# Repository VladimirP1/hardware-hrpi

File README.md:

# A simple add-on board for Raspberry Pi to run a downstream verion of APM (https://github.com/VladimirP1/ardupilot) (waf configure --board=hrpi)

This board has been designed considering this technology: http://cxem.net/master/45.php

The APM port requires servod form ServoBlaster (https://github.com/richardghirst/PiBits/tree/master/ServoBlaster/user) to be in PATH.

Only one hardware UART is available on the Pi, so either GPS or telemetry should be connected over USB.

# RT-preempt
- I have built my RT kernel from official Rasberry Pi Foundation's kernel patched with corresponding RT version.
- If your pi does not boot with RT-patched kernel try adding sdhci_bcm2708.enable_llm=0 to cmdline. If you expirince hangs with RT kernel try to add dwc_otg.fiq_enable=0 to cmdline.

# WARNING
-This board uses 10k resistors to protect Raspberry pi's inputs from 5v and relies on its internal protection diodes.
Earlier revision of the board with external diodes work OK, but the current revision is UNTESTED.

-ALWAYS FLASH FIRMWARE BEFORE PLUGGING IN ARDUINO NANO OR YOU RISK TO BURN YOUR PI (It can happen if either of A4 and A5 is driven HIGH) !!!

-Only tested on RPI 2

# Repo structure
- doc: documentation
- src/kicad/hrpi: KICAD sources
- src/arduino/i2c-adc-rc: Arduino sources

# Important notes
- MPU6000 uses MOSI, MISO, SCLK, NSS2, GND, 3V3 form the SPI connector.

# Details
- RC input is recieved by arduino nano, then it is read out by RPI over i2c.
- RC output is done over RPI's gpio using ServoBlaster (https://github.com/richardghirst/PiBits/tree/master/ServoBlaster/user).
- Sensors must be connected externally by SPI and I2C. Madarnatory sensors: MPU6000(SPI), HMC5883L(I2C), MS5611(I2C, except rover).
Examples of breakout boards: GY-63, GY-273 and Mikroe MPU imu click.
- Power must be provided either over the RC rail with P9 closed or the P3 connector

# Serial pinout

# Connecting 3DR radio

If you have two ground modules you can plug one into your PC, one into RPI. They will communicate.
If they do not, make sure that the have same net id.
You can also connect to RPI without 3DR radio, over wifi.

# I2C pinout

# SPI pinout

# How to connect ACC/GYRO

# ADC pinout

# RC main pinout

# RC aux pinout
AUX0-AUX4=RC8-RC13

# Todo
- handle RC OK led by software
- maybe upstream APM
- fix default accel orientation

# Render

# License
The repo contents are licensed under the MIT license

Copyright (c) 2016 Vladimir Pinchuk

Permission is hereby granted, free of charge, to any person obtaining a copy of this software and associated documentation files (the "Software"), to deal 
in the Software without restriction, including without limitation the rights to use, copy, modify, merge, publish, distribute, sublicense, and/or sell copies of 
the Software, and to permit persons to whom the Software is furnished to do so, subject to the following conditions:

The above copyright notice and this permission notice shall be included in all copies or substantial portions of the Software.

THE SOFTWARE IS PROVIDED "AS IS", WITHOUT WARRANTY OF ANY KIND, EXPRESS OR IMPLIED, INCLUDING BUT NOT LIMITED TO THE WARRANTIES OF MERCHANTABILITY, FITNESS 
FOR A PARTICULAR PURPOSE AND NONINFRINGEMENT. IN NO EVENT SHALL THE AUTHORS OR COPYRIGHT HOLDERS BE LIABLE FOR ANY CLAIM, DAMAGES OR OTHER LIABILITY, WHETHER IN 
AN ACTION OF CONTRACT, TORT OR OTHERWISE, ARISING FROM, OUT OF OR IN CONNECTION WITH THE SOFTWARE OR THE USE OR OTHER DEALINGS IN THE SOFTWARE.

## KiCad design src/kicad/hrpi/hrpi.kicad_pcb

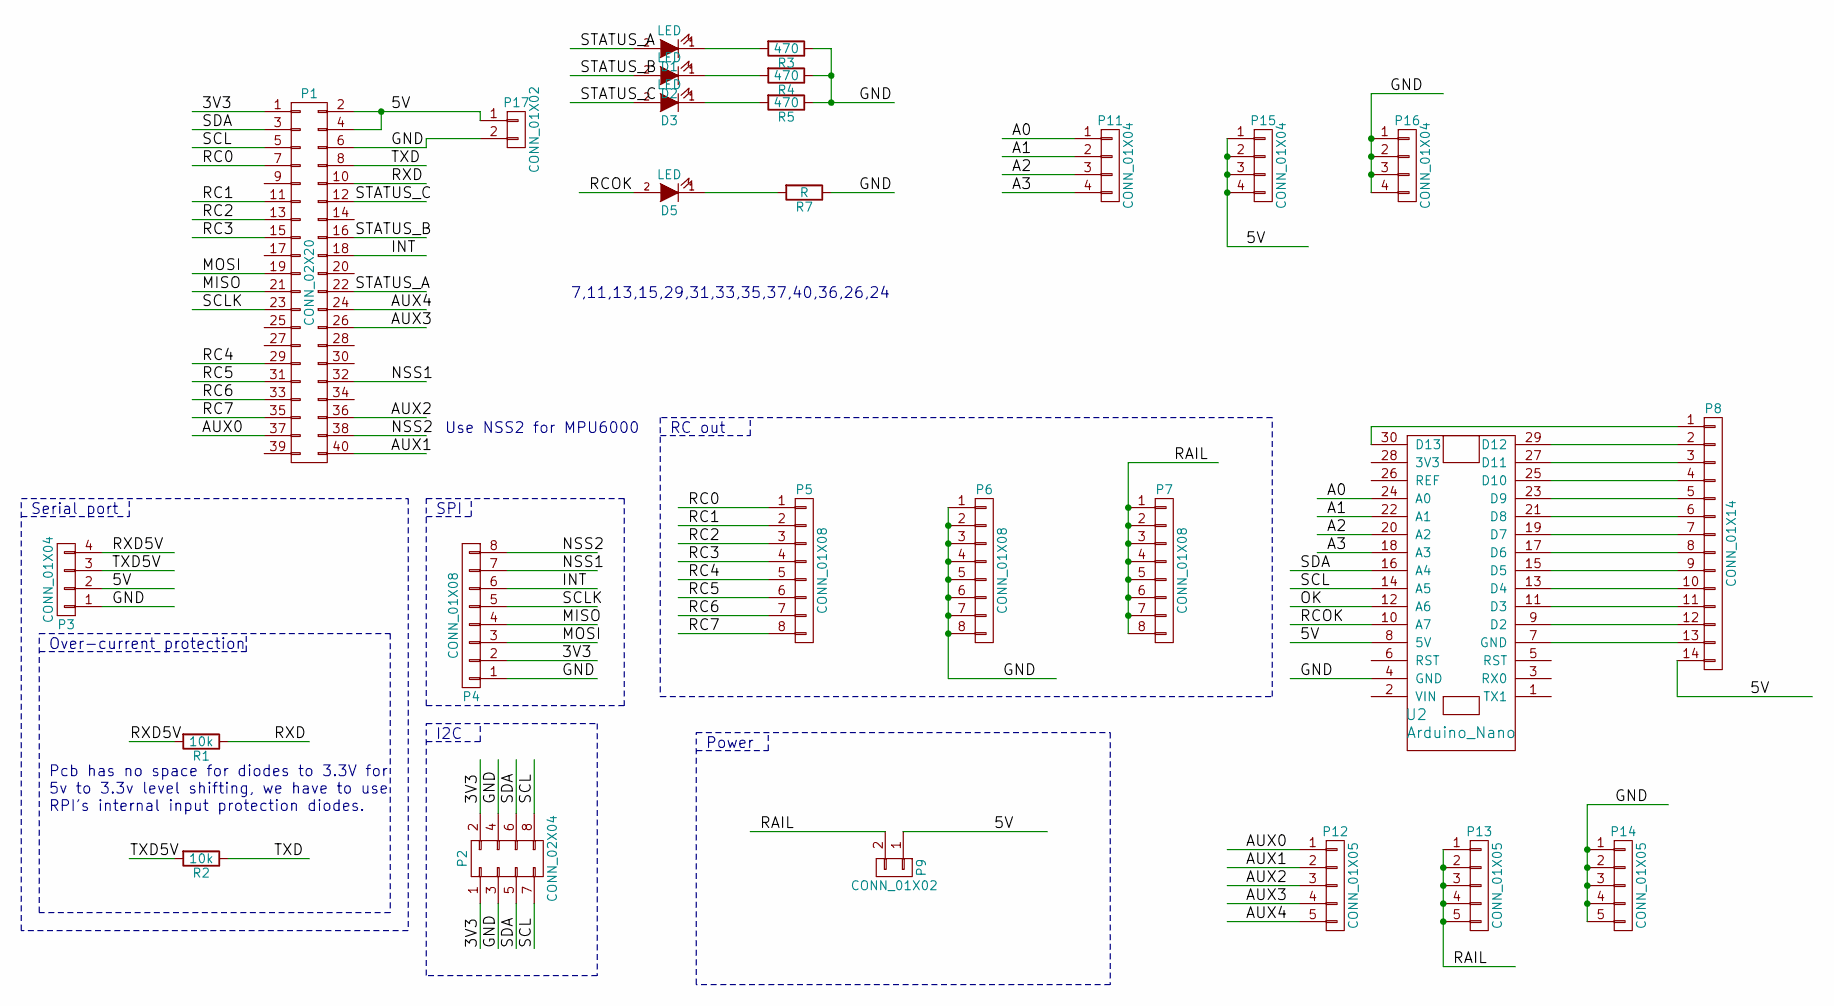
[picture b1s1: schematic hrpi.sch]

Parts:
D1, D2, D3, D5: LED; LED-3MM
P1: CONN_02X20; Pin_Header_Straight_2x20
P2: CONN_02X04; Pin_Header_Straight_2x04
P3, P11, P15, P16: CONN_01X04; Pin_Header_Straight_1x04
P4, P5, P6, P7: CONN_01X08; Pin_Header_Straight_1x08
P8: CONN_01X14; Pin_Header_Straight_1x14
P9, P17: CONN_01X02; Pin_Header_Straight_1x02
P12, P13, P14: CONN_01X05; Pin_Header_Straight_1x05
R1, R2: 10k; R_0805_HandSoldering
R3, R4, R5: 470; R_0805_HandSoldering
R7: R; R_0805_HandSoldering
U2: Arduino_Nano; arduino_nano

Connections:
/3V3: P1.1, P2.1, P2.2, P4.2
/5V: P1.2, P1.4, P3.2, P8.14, P9.1, P15.1, P15.2, P15.3, P15.4, P17.1, U2.8 (5V)
/A0: P11.1, U2.24 (A0)
/A1: P11.2, U2.22 (A1)
/A2: P11.3, U2.20 (A2)
/A3: P11.4, U2.18 (A3)
/AUX0: P1.37, P12.1
/AUX1: P1.40, P12.2
/AUX2: P1.36, P12.3
/AUX3: P1.26, P12.4
/AUX4: P1.24, P12.5
/GND: P1.6, P2.3, P2.4, P3.1, P4.1, P6.1, P6.2, P6.3, P6.4, P6.5, P6.6, P6.7, P6.8, P14.1, P14.2, P14.3, P14.4, P14.5, P16.1, P16.2, P16.3, P16.4, P17.2, R3.1, R4.1, R5.1, R7.1, U2.4 (GND)
/INT: P1.18, P4.6
/MISO: P1.21, P4.4
/MOSI: P1.19, P4.3
/NSS1: P1.32, P4.7
/NSS2: P1.38, P4.8
/RAIL: P7.1, P7.2, P7.3, P7.4, P7.5, P7.6, P7.7, P7.8, P9.2, P13.1, P13.2, P13.3, P13.4, P13.5
/RC0: P1.7, P5.1
/RC1: P1.11, P5.2
/RC2: P1.13, P5.3
/RC3: P1.15, P5.4
/RC4: P1.29, P5.5
/RC5: P1.31, P5.6
/RC6: P1.33, P5.7
/RC7: P1.35, P5.8
/RCOK: D5.2 (A), U2.10 (A7)
/RXD: P1.10, R1.1
/RXD5V: P3.4, R1.2
/SCL: P1.5, P2.7, P2.8, U2.14 (A5)
/SCLK: P1.23, P4.5
/SDA: P1.3, P2.5, P2.6, U2.16 (A4)
/STATUS_A: D1.2 (A), P1.22
/STATUS_B: D2.2 (A), P1.16
/STATUS_C: D3.2 (A), P1.12
/TXD: P1.8, R2.1
/TXD5V: P3.3, R2.2
unnamed: D1.1 (K), R3.2
unnamed: D2.1 (K), R4.2
unnamed: D3.1 (K), R5.2
unnamed: D5.1 (K), R7.2
unnamed: P8.1, U2.30 (D13)
unnamed: P8.2, U2.29 (D12)
unnamed: P8.3, U2.27 (D11)
unnamed: P8.4, U2.25 (D10)
unnamed: P8.5, U2.23 (D9)
unnamed: P8.6, U2.21 (D8)
unnamed: P8.7, U2.19 (D7)
unnamed: P8.8, U2.17 (D6)
unnamed: P8.9, U2.15 (D5)
unnamed: P8.10, U2.13 (D4)
unnamed: P8.11, U2.11 (D3)
unnamed: P8.12, U2.9 (D2)
unnamed: P8.13, U2.7 (GND)

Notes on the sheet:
Over-current protection
Serial port
I2C
SPI
Use NSS2 for MPU6000
RC out
Power
Pcb has no space for diodes to 3.3V for 5v to 3.3v level shifting, we have to use RPI's internal input protection diodes.
7,11,13,15,29,31,33,35,37,40,36,26,24

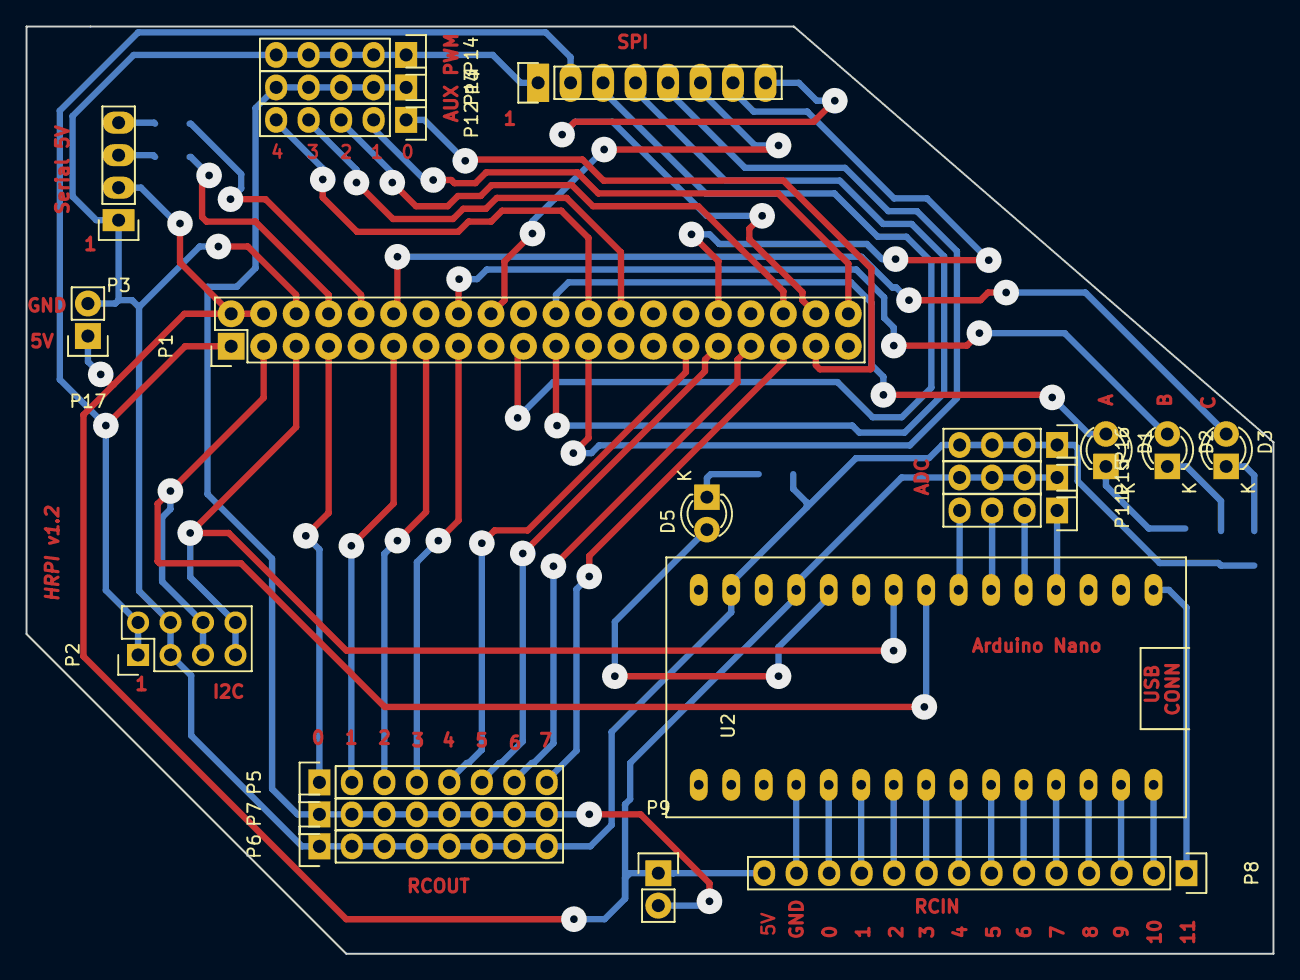
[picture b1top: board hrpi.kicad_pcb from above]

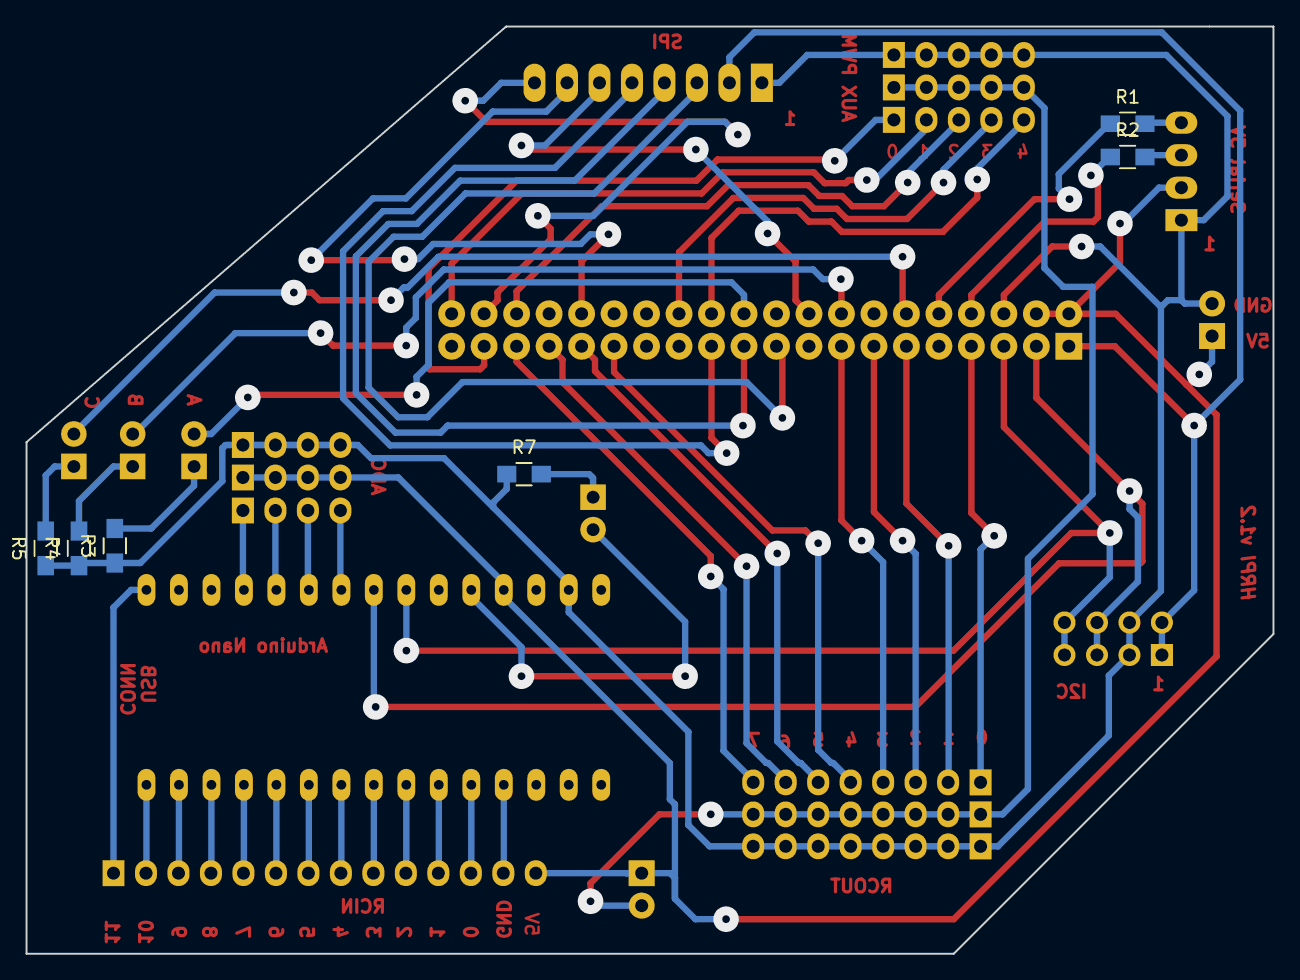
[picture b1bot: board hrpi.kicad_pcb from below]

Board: 2 copper layers, 97.5 x 72.5 mm, 27 parts (6 on the bottom side), 54 nets.

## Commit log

2016-06-20 Initial commit of HRPI design files.
2016-06-20 Improved HRPI
2016-06-21 Move submodule to main repo
2016-06-21 Input channel count increased in hardware, but not in software
2016-06-21 Status leds added to hardware
2016-06-21 Bugs fixed, added 5v connector
2016-06-22 Added board render
2016-06-22 Updated render
2016-06-22 Files reordered
2016-06-22 Fixed typo
2016-06-22 Updated doc
2016-06-22 Added 12 channel untested pwm to i2c encoder code
2016-06-22 BUGFIX
2016-06-22 remove scheme.png
2016-06-23 doc updated
2016-06-24 README.md updated
2016-06-30 Replaced power jumper
2016-06-30 Some traces moved
